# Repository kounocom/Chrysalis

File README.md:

# Chrysalis

**A shield PCB for the nRF52840 Supermini/Pro Micro with an IMU, magnetometer, two buttons and a RGB LED, designed for nRF-based SlimeVR trackers**

## Overview

Chrysalis is a compact, back-mounted shield that solders directly to the underside of the nRF52840 Supermini or Pro Micro. It adds:

- 3-axis accelerometer/gyroscope (TDK InvenSense ICM-45686)  
- 3-axis magnetometer (QMC6309)  
- Two push-buttons for SW0 and RESET 
- Configurable RGB LED (Currently requires custom built firmware for changing the color)
- Pads for battery wires 

All exposed pads are marked with a star (`*`) and **must** be soldered.

## Requirements

- Assembled Chrysalis board
- nRF52840 Supermini or Pro Micro  
- Soldering iron (chisel or knife-type tip recommended), solder wire, flux (optional but recommended)

## Ordering Information

Chrysalis requires:
- Castellated holes on two sides  
- ENIG surface finish (for the QMC6309 BGA pads)  
- Thin PCB stack-up (0.8 mm or 1.0 mm recommended)

Manufacturing is most cost-effective at volume. For small quantities, consider ordering from [here](https://nekumori.pink/products/chysalis-v1_3).

## Hardware Assembly

1. **Prepare the Supermini**  
   - Update your bootloader **before** soldering and verify functionality. SWD pads will be covered after soldering, so unbricking/recovery will require removing the shield.  

2. **Align Chrysalis**  
   - Flip the Supermini upside-down (chips side down).  
   - Match the silkscreen markers on the backside of Chrysalis:  
     - **USB above** → near the USB connector 
     - **Antenna below** → near the antenna

3. **Solder Every Exposed Pad**  
   - All castellated pads are marked with `*`.  
   - Tack one corner pad to secure alignment, then solder the rest.  
   - Use direct solder connections—no wires or pin-headers.  
   - Inspect joints under magnification; check for cold or dry joints and bridges.

4. **Consider the Wire-Mod for the Pro-Micro Antenna**
   - https://docs.slimevr.dev/smol-slimes/hardware/smol-tracker.html#-copper-wire-for-wire-antenna-mod

## Pinout & Connections

| Supermini Pin | Signal    |
|---------------|-----------|
| P0.17         | IMU INT1  |
| P0.24         | MISO      |
| P0.06         | MOSI      |
| P0.08         | SCK       |
| P0.22         | CS        |
| P1.00         | SW0       |
| RST / P0.18   | RESET     |
| P0.20         | CLK_CTL   |
| GND           | GND       |
| P0.31         | VCC       |
| P0.02         | R         |
| P1.15         | G         |
| P0.29         | B         |

> **Note:**  
> - The module intentionally sources power from one of the nRF52840's GPIOs (P0.31), as the voltage of it is adjustable.
> - The QMC6309 requires a minimum supply voltage of 2.5 V.

_For the complete schematic and up-to-date pin mapping, see `Chrysalis.kicad_sch`._

## Usage

1. Plug the assembled Supermini+Chrysalis combo into your host via USB.  
2. Flash the Slime-nRF Chrysalis firmware:   
   - Download the pre-compiled firmware:  
     https://docs.slimevr.dev/smol-slimes/firmware/smol-pre-compiled-firmware.html#pcb 
    - Follow the guide:  
     https://docs.slimevr.dev/smol-slimes/firmware/smol-flashing-firmware.html 
3. Open a serial console to verify IMU, magnetometer and button functionality.

> **Note:**  
> - At the time of writing this, the magnetometer will not be detected, because the IMU's sensorhub functionality has not been fully implemented.

## License

This project is licensed under the CERN Open Hardware Licence 2.0 – Strongly Reciprocal (CERN-OHL-S).  
See `LICENSE.md` for full terms

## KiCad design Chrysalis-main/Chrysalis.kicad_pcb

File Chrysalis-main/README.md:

# Chrysalis

**A shield PCB for the nRF52840 Supermini/Pro Micro with an IMU, magnetometer, two buttons and a RGB LED, designed for nRF-based SlimeVR trackers**

## Overview

Chrysalis is a compact, back-mounted shield that solders directly to the underside of the nRF52840 Supermini or Pro Micro. It adds:

- 3-axis accelerometer/gyroscope (TDK InvenSense ICM-45686)  
- 3-axis magnetometer (QMC6309)  
- Two push-buttons for SW0 and RESET 
- Configurable RGB LED (Currently requires custom built firmware for changing the color)
- Pads for battery wires 

All exposed pads are marked with a star (`*`) and **must** be soldered.

## Requirements

- Assembled Chrysalis board
- nRF52840 Supermini or Pro Micro  
- Soldering iron (chisel or knife-type tip recommended), solder wire, flux (optional but recommended)

## Ordering Information

Chrysalis requires:
- Castellated holes on two sides  
- ENIG surface finish (for the QMC6309 BGA pads)  
- Thin PCB stack-up (0.8 mm or 1.0 mm recommended)

Manufacturing is most cost-effective at volume. For small quantities, consider ordering from [here](https://nekumori.pink/products/chysalis-v1_3).

## Hardware Assembly

1. **Prepare the Supermini**  
   - Update your bootloader **before** soldering and verify functionality. SWD pads will be covered after soldering, so unbricking/recovery will require removing the shield.  

2. **Align Chrysalis**  
   - Flip the Supermini upside-down (chips side down).  
   - Match the silkscreen markers on the backside of Chrysalis:  
     - **USB above** → near the USB connector 
     - **Antenna below** → near the antenna

3. **Solder Every Exposed Pad**  
   - All castellated pads are marked with `*`.  
   - Tack one corner pad to secure alignment, then solder the rest.  
   - Use direct solder connections—no wires or pin-headers.  
   - Inspect joints under magnification; check for cold or dry joints and bridges.

4. **Consider the Wire-Mod for the Pro-Micro Antenna**
   - https://docs.slimevr.dev/smol-slimes/hardware/smol-tracker.html#-copper-wire-for-wire-antenna-mod

## Pinout & Connections

| Supermini Pin | Signal    |
|---------------|-----------|
| P0.17         | IMU INT1  |
| P0.24         | MISO      |
| P0.06         | MOSI      |
| P0.08         | SCK       |
| P0.22         | CS        |
| P1.00         | SW0       |
| RST / P0.18   | RESET     |
| P0.20         | CLK_CTL   |
| GND           | GND       |
| P0.31         | VCC       |
| P0.02         | R         |
| P1.15         | G         |
| P0.29         | B         |

> **Note:**  
> - The module intentionally sources power from one of the nRF52840's GPIOs (P0.31), as the voltage of it is adjustable.
> - The QMC6309 requires a minimum supply voltage of 2.5 V.

_For the complete schematic and up-to-date pin mapping, see `Chrysalis.kicad_sch`._

## Usage

1. Plug the assembled Supermini+Chrysalis combo into your host via USB.  
2. Flash the Slime-nRF Chrysalis firmware:   
   - Download the pre-compiled firmware:  
     https://docs.slimevr.dev/smol-slimes/firmware/smol-pre-compiled-firmware.html#pcb 
    - Follow the guide:  
     https://docs.slimevr.dev/smol-slimes/firmware/smol-flashing-firmware.html 

3. Open a serial console to verify IMU, magnetometer and button functionality.

> **Note:**  
> - At the time of writing this, the magnetometer will not be detected, because the IMU's sensorhub functionality has not been fully implemented.

## License

This project is licensed under the CERN Open Hardware Licence 2.0 – Strongly Reciprocal (CERN-OHL-S).  
See `LICENSE.md` for full terms

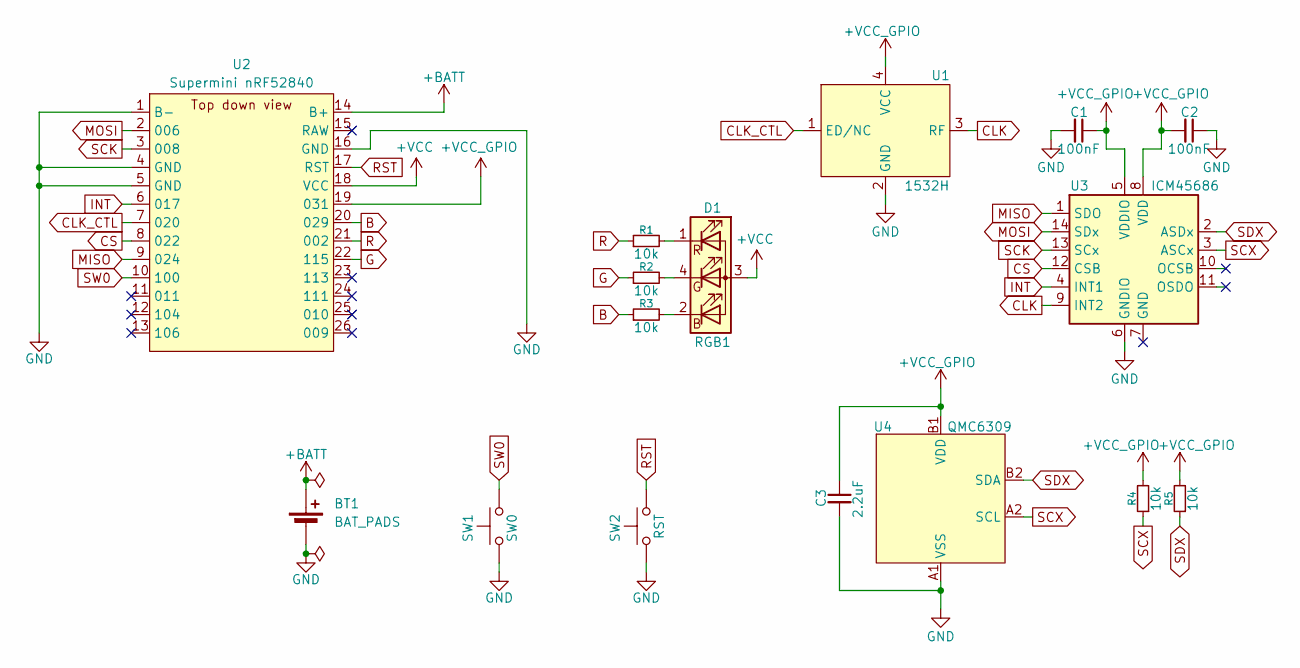
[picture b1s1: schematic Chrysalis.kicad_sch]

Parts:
BT1: BAT_PADS; Bat_Pads; MPN N/A
C1, C2: 100nF; C_0402; MPN C1525
C3: 2.2uF; C_0603; MPN C57895
D1: RGB1; LED-ARRAY-SMD_4P-L2.1-W2.1-TL_NH-B2020RGBA; MPN C2874116
R1, R2, R3, R4, R5: 10k; R_0402; MPN C25744
SW1: SW0; SW-SMD_4P-L5.1-W5.1-P3.70-LS6.5-TL_H1.5; MPN C318884
SW2: RST; SW-SMD_L3.0-W2.0-LS3.5; MPN C778126
U1: 1532H; CLK; MPN C709192
U2: Supermini nRF52840; MPN N/A
U3: ICM45686; IMU; MPN C22459454
U4: QMC6309; MPN C5439871

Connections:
+BATT: BT1.1 (+), U2.14 (B+)
+VCC: D1.3 (A), U2.18 (VCC)
+VCC_GPIO: C1.1, C2.2, C3.1, R4.2, R5.2, U1.4 (VCC), U2.19 (031), U3.5 (VDDIO), U3.8 (VDD), U4.B1 (VDD)
B: R3.1, U2.20 (029)
CLK: U1.3 (RF), U3.9 (INT2)
CLK_CTL: U1.1 (ED/NC), U2.7 (020)
CS: U2.8 (022), U3.12 (CSB)
G: R2.1, U2.22 (115)
GND: BT1.2 (-), C1.2, C2.1, C3.2, SW1.1, SW2.1, U1.2 (GND), U2.1 (B-), U2.4 (GND), U2.5 (GND), U2.16 (GND), U3.6 (GNDIO), U4.A1 (VSS)
INT: U2.6 (017), U3.4 (INT1)
MISO: U2.9 (024), U3.1 (SDO)
MOSI: U2.2 (006), U3.14 (SDx)
unnamed: D1.2 (BK), R3.2
unnamed: D1.4 (GK), R2.2
unnamed: D1.1 (RK), R1.2
R: R1.1, U2.21 (002)
RST: SW2.2, U2.17 (RST)
SCK: U2.3 (008), U3.13 (SCx)
SCX: R4.1, U3.3 (ASCx), U4.A2 (SCL)
SDX: R5.1, U3.2 (ASDx), U4.B2 (SDA)
SW0: SW1.2, U2.10 (100)

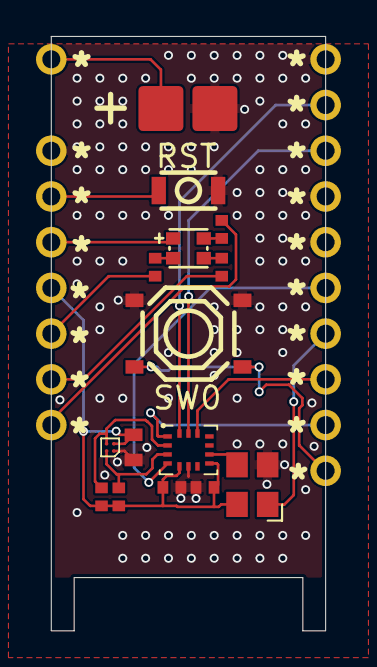
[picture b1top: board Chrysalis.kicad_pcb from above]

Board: 2 copper layers, 15.2 x 33.0 mm, 16 parts (1 on the bottom side), 21 nets.

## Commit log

2025-08-05 Initial
2025-10-15 Update to include Chrysalis Solder Helper Updated information
2025-10-15 Fix the Duplicated Files
